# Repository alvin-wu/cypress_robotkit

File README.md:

# cypress_robotkit
Alvin Wu | Todd Nguyen | Byung Joo Park  
University of Illinois Urbana Champaign 

Autonomous Robot kit developed as a University of Illinois Senior Design project for Cypress Semiconductor. 

~ Winner of the Fall 2016 Instructor's Award ~

~ Featured as Cypress' Maker of the Month ~ &nbsp;
http://core.cypress.com/cypress-maker-of-the-month-alvin-wu-and-todd-nguyen/#.WR6BGmjyu7P

This repository contains the open-sourced material to build your own robot kit. 
It includes three separated folders with the firmware code, the Android phone application, as well as Eagle schematics respectively.

## Instructions
The firmware code has already been packaged into a project folder in robot_kit_firmware.cydsn. To open this project, download PSoC Creator and simply open this project folder.

Similarly, to open the Android project folder, use Android Studio and select this folder as the project you wish to use.

## Motivation 
New market of makers and hobbyists.

Popular products such as Arduino or Raspberry Pi for projects.

Alternative: PSoC 

## Objectives & Features
Goal: Design and build a robot kit to demonstrate the capabilities of the PSoC

* “Kit-able” design with easy construction

* Inexpensive to make it more accessible for hobbyist (under $150)

* Plug-and-play experience to demonstrate the PSoC capabilities 

## Features
* Mountable shield that provides power system, motor control, and sensors for PSoC.

* Remote control using Bluetooth Low Energy (BLE) and phone application.

* Ability to switch between manual control and autonomous modes on the phone application .

* Autonomous obstacle avoidance using sonar sensor.

* Autonomous line following with IR emitting sensors.

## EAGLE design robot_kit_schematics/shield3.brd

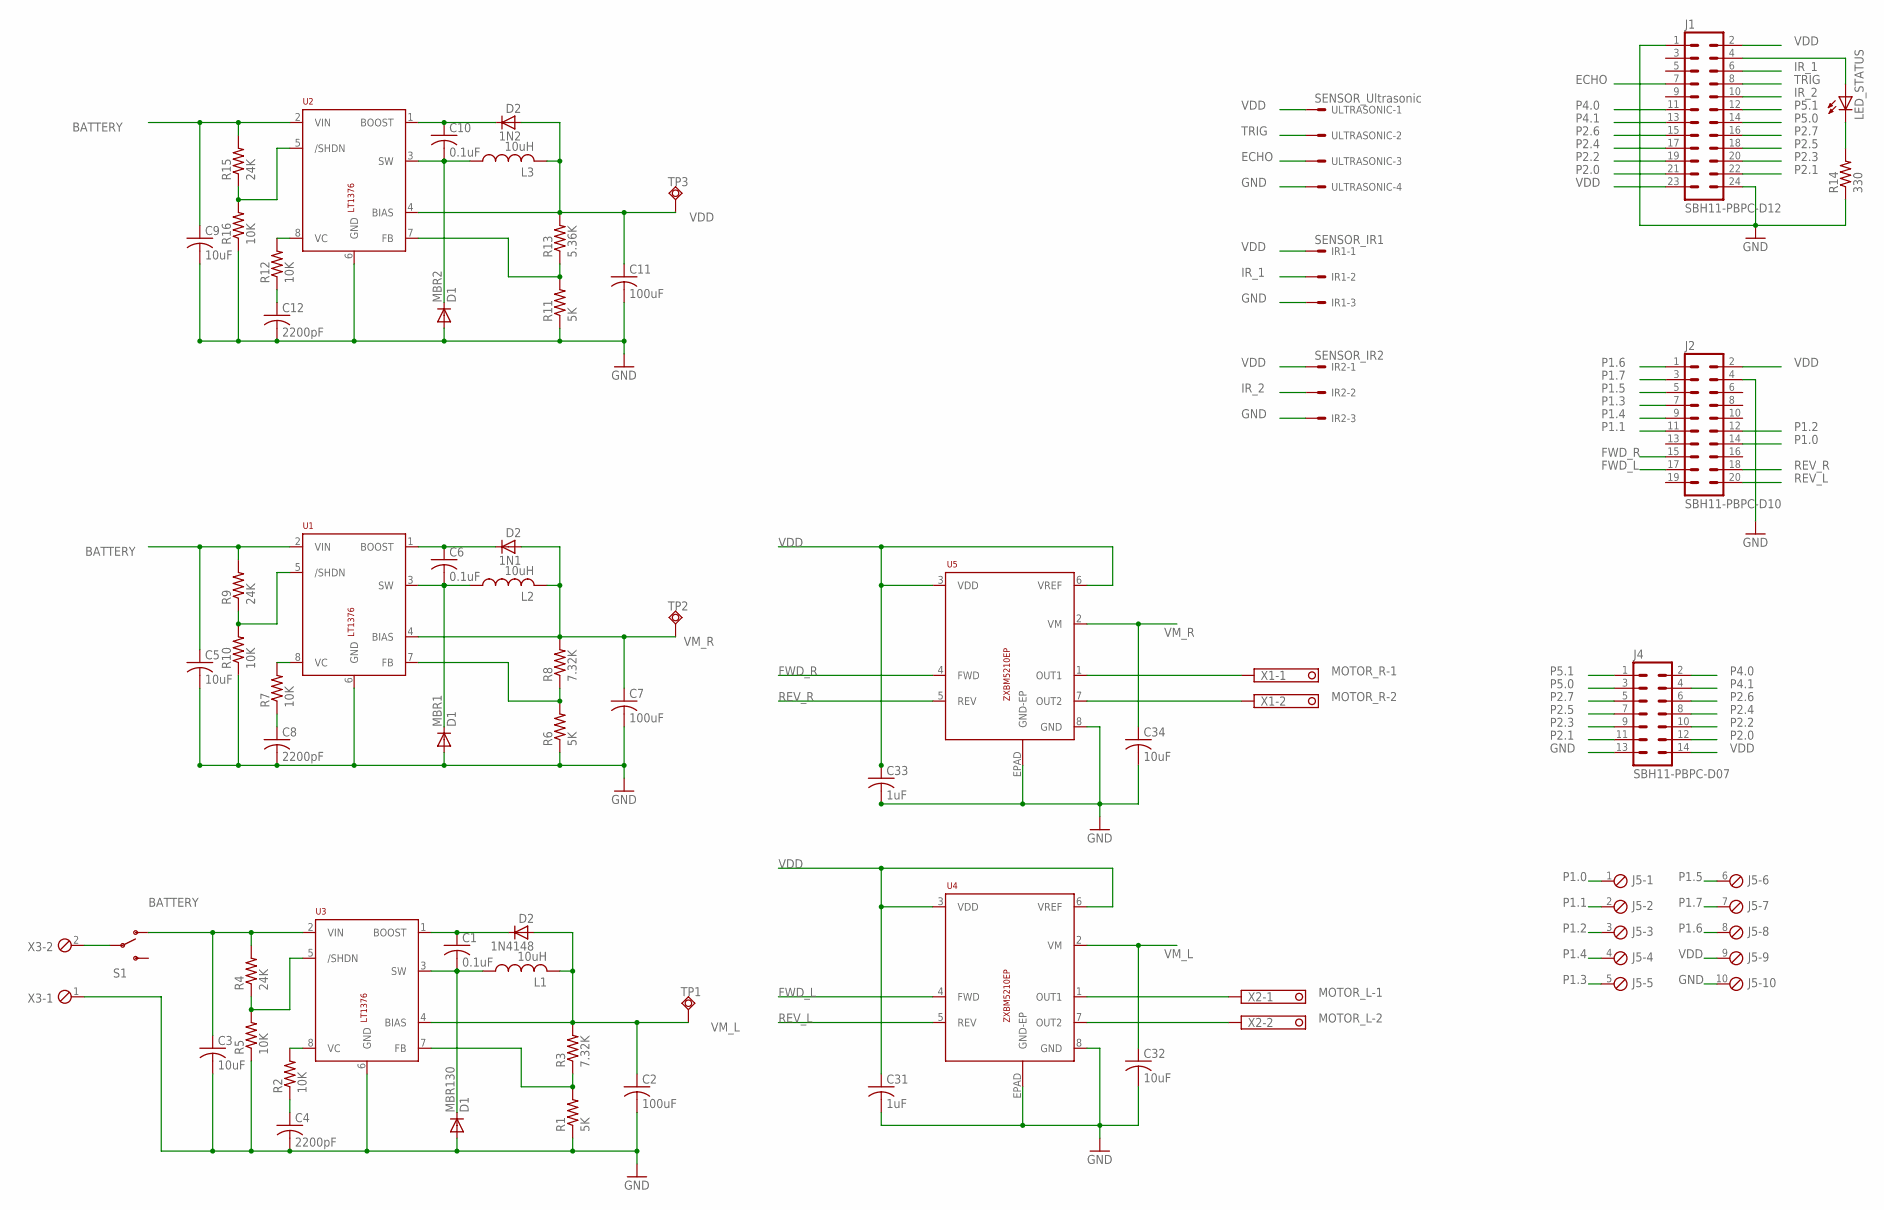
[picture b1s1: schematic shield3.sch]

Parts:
1N1, 1N2, 1N4148: D2; SOD123
C1, C6, C10: 0.1uF; C1206
C2, C7, C11: 100uF; C1206
C3, C5, C9: 10uF; C1206
C4, C8, C12: 2200pF; C1206
C31, C33: 1uF; C3216
C32, C34: 10uF; C3216
IR1: SENSOR_IR1; 6410-03
IR2: SENSOR_IR2; 6410-03
J1: SBH11-PBPC-D12
J2: SBH11-PBPC-D10
J4: SBH11-PBPC-D07
J5: MPT10; 10POL254
L1, L2, L3: 10uH; L4035M
LED_STATUS: LED_E; LED_1206
MBR1, MBR2, MBR130: D1; SOD123
R1, R6, R11: 5K; M3216
R2, R5, R7, R10, R12, R16: 10K; M3216
R3, R8: 7.32K; M3216
R4, R9, R15: 24K; M3216
R13: 5.36K; M3216
R14: 330; M3216
S1: SWITCH-SPDTPTH; SWITCH-SPDT
TP1, TP2, TP3: TPSQPAD1-13; P1-13
U1, U2, U3: LT1376; S8
U4, U5: ZXBM5210EP; SO08-EPAD
ULTRASONIC: SENSOR_Ultrasonic; 6410-04
X1, X2: 1751248
X3: MPT2; 2POL254

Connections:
BATTERY: C3.1, C5.1, C9.1, R4.2, R9.2, R15.2, S1.1 (O), U1.2 (VIN), U2.2 (VIN), U3.2 (VIN)
ECHO: J1.7, ULTRASONIC.3
FWD_L: J2.17, U4.4 (FWD)
FWD_R: J2.15, U5.4 (FWD)
GND: C2.2, C3.2, C4.2, C5.2, C7.2, C8.2, C9.2, C11.2, C12.2, C31.2, C32.2, C33.2, C34.2, IR1.3, IR2.3, J1.1, J1.24, J2.4, J4.13, J5.10, MBR1.A, MBR2.A, MBR130.A, R1.1, R5.1, R6.1, R10.1, R11.1, R14.1, R16.1, U1.6 (GND), U2.6 (GND), U3.6 (GND), U4.8 (GND), U4.EPAD (GND-EP), U5.8 (GND), U5.EPAD (GND-EP), ULTRASONIC.4, X3.1
IR_1: IR1.2, J1.6
IR_2: IR2.2, J1.10
MOTOR_L-1: U4.1 (OUT1), X2.1
MOTOR_L-2: U4.7 (OUT2), X2.2
MOTOR_R-1: U5.1 (OUT1), X1.1
MOTOR_R-2: U5.7 (OUT2), X1.2
unnamed: C1.2, L1.1, MBR130.C, U3.3 (SW)
unnamed: R4.1, R5.2, U3.5 (/SHDN)
unnamed: R1.2, R3.1, U3.7 (FB)
unnamed: LED_STATUS.C, R14.2
unnamed: 1N1.1 (C), C6.1, U1.1 (BOOST)
unnamed: J1.4, LED_STATUS.A
unnamed: C6.2, L2.1, MBR1.C, U1.3 (SW)
unnamed: R7.2, U1.8 (VC)
unnamed: C8.1, R7.1
unnamed: R6.2, R8.1, U1.7 (FB)
unnamed: R9.1, R10.2, U1.5 (/SHDN)
unnamed: 1N2.1 (C), C10.1, U2.1 (BOOST)
unnamed: 1N4148.1 (C), C1.1, U3.1 (BOOST)
unnamed: C10.2, L3.1, MBR2.C, U2.3 (SW)
unnamed: R2.2, U3.8 (VC)
unnamed: C4.1, R2.1
unnamed: R12.2, U2.8 (VC)
unnamed: C12.1, R12.1
unnamed: R11.2, R13.1, U2.7 (FB)
unnamed: R15.1, R16.2, U2.5 (/SHDN)
unnamed: S1.2, X3.2
P1.0: J2.14, J5.1
P1.1: J2.11, J5.2
P1.2: J2.12, J5.3
P1.3: J2.7, J5.5
P1.4: J2.9, J5.4
P1.5: J2.5, J5.6
P1.6: J2.1, J5.8
P1.7: J2.3, J5.7
P2.0: J1.21, J4.12
P2.1: J1.22, J4.11
P2.2: J1.19, J4.10
P2.3: J1.20, J4.9
P2.4: J1.17, J4.8
P2.5: J1.18, J4.7
P2.6: J1.15, J4.6
P2.7: J1.16, J4.5
P4.0: J1.11, J4.2
P4.1: J1.13, J4.4
P5.0: J1.14, J4.3
P5.1: J1.12, J4.1
REV_L: J2.20, U4.5 (REV)
REV_R: J2.18, U5.5 (REV)
TRIG: J1.8, ULTRASONIC.2
VDD: 1N2.2 (A), C11.1, C31.1, C33.1, IR1.1, IR2.1, J1.2, J1.23, J2.2, J4.14, J5.9, L3.2, R13.2, TP3.TP, U2.4 (BIAS), U4.3 (VDD), U4.6 (VREF), U5.3 (VDD), U5.6 (VREF), ULTRASONIC.1
VM_L: 1N4148.2 (A), C2.1, C32.1, L1.2, R3.2, TP1.TP, U3.4 (BIAS), U4.2 (VM)
VM_R: 1N1.2 (A), C7.1, C34.1, L2.2, R8.2, TP2.TP, U1.4 (BIAS), U5.2 (VM)

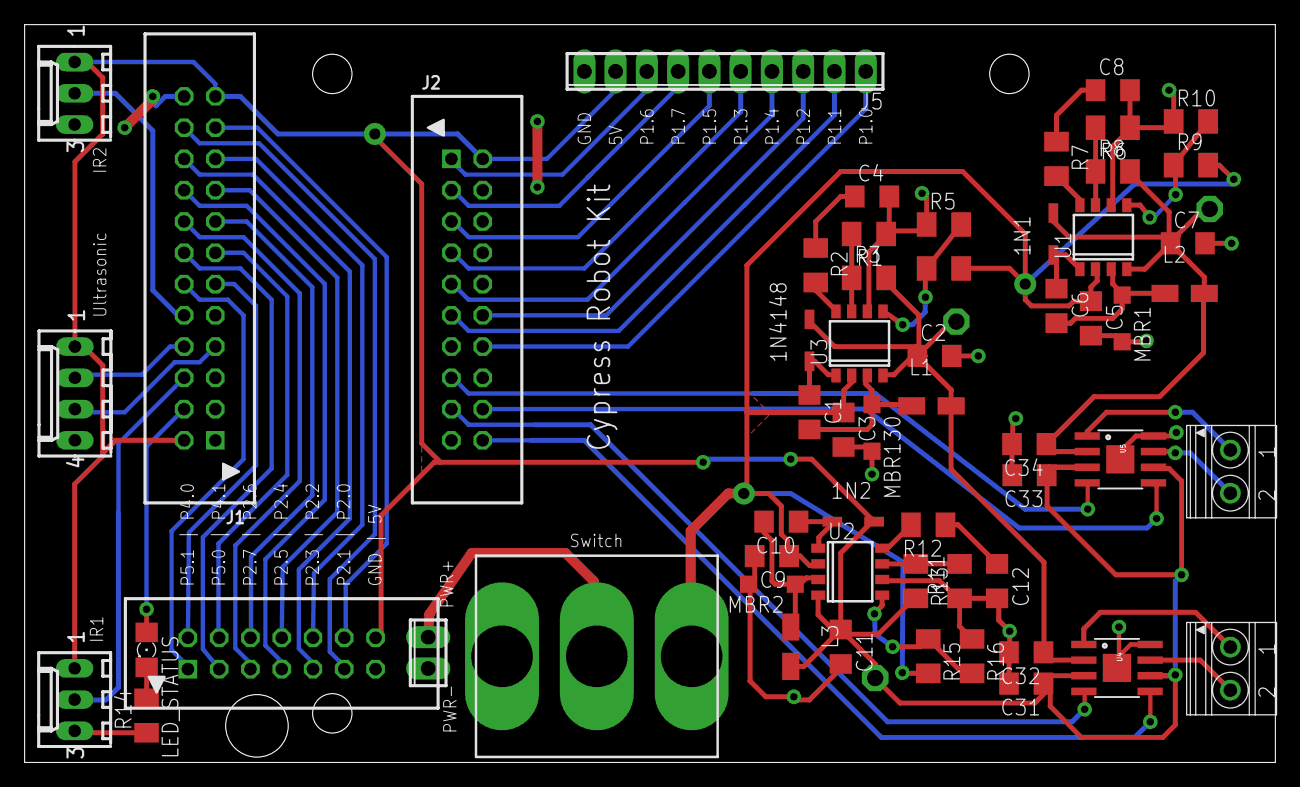
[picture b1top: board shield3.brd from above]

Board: 2 copper layers, 101.6 x 59.9 mm, 61 parts (0 on the bottom side), 58 nets.

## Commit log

2017-02-26 added project

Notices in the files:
parts and their libraries:
con-sullins: Copyright (C) 2009, Bob Starr
